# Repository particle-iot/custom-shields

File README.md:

custom-shields
==============

Collection of design files for the Spark powered custom shields

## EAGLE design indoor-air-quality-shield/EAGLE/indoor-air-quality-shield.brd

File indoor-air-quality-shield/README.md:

# Indoor Air Quality Shield

### Specifications:
 * Sensors:
 	1. Figaro TGS 2602 VOC Sensor
 	2. MICS-5525 Carbon Monoxide (CO) Sensor
 	3. DHT22 Humidity and Temperature Sensor
 	4. 2 Sockets of MQ Series Sensors
 	5. 2 Ports for Grove Sensors
 * User defined RGB LED
 * Two calibration buttons
 * Serial Port breakout headers
 * On-board DC-DC 5V power regulator

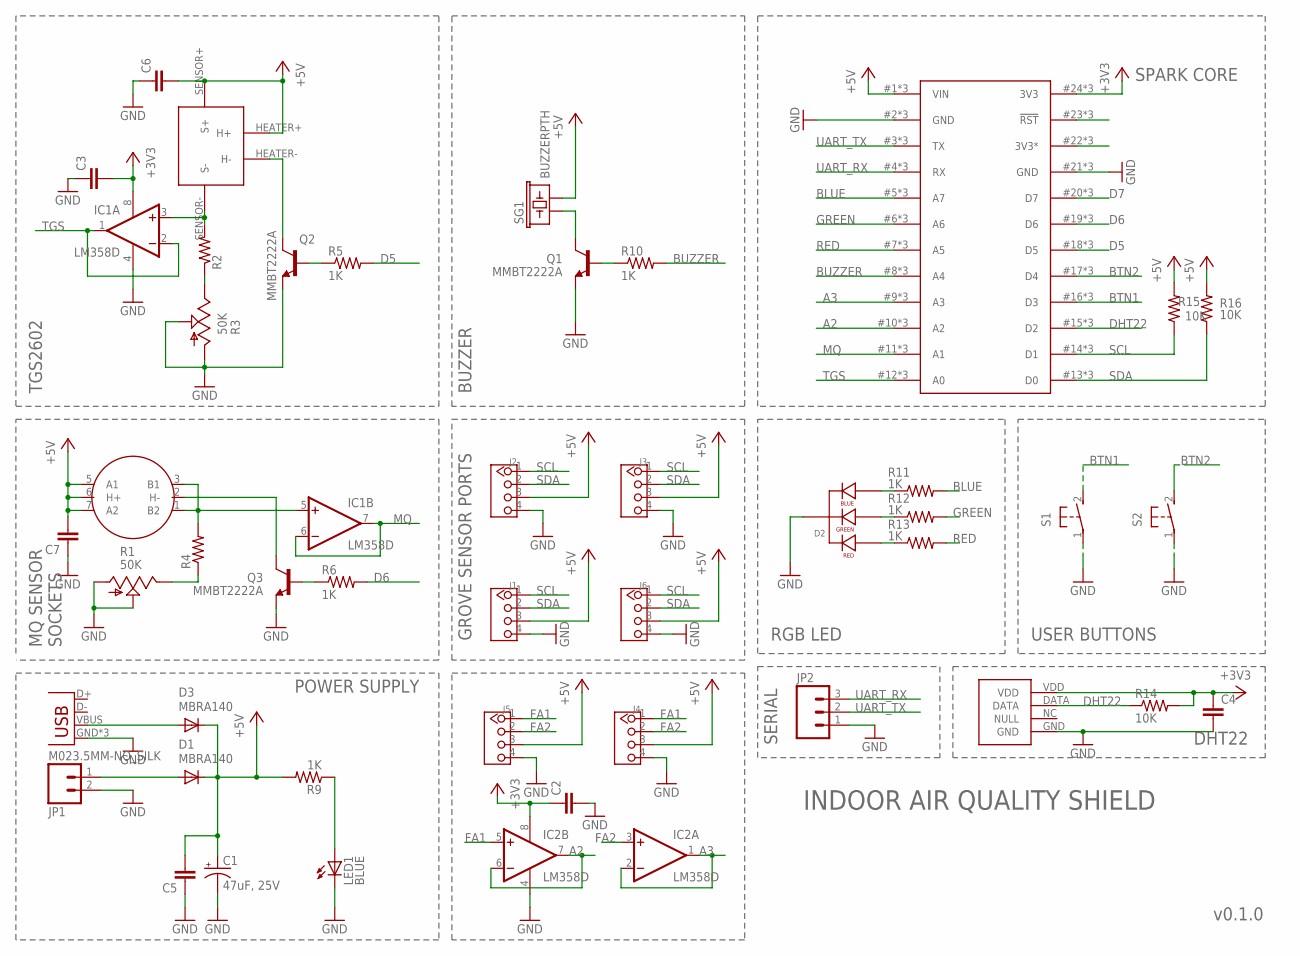
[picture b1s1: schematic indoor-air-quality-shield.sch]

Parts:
C1: 47uF, 25V; PANASONIC_D
C2, C3, C4, C5, C6, C7: C-EUC0603; C0603
D1, D3: MBRA140; SMA-DIODE
D2: LED-RGB-CC-THRUCLEAR; LED-RGB-THRU
IC1, IC2: LM358D; SO08
J1, J2, J3, J4, J5, J6: TWIG-4P-2.0'D90'; 4P-2.0-90D-W/O-BUCKLE
JP1: M023.5MM-NO_SILK; SCREWTERMINAL-3.5MM-2-NS
JP2: M03PTH; 1X03
JP3: USBUSB-MICROB-SLOT-HOLE; USB-MICROB-SLOT-HOLE
LED1: BLUE; LED-0603
Q1, Q2, Q3: MMBT2222A; SOT23-3
R1, R3: 50K; RJ9W
R2, R4: RESISTOR0603; 0603-RES
R5, R6, R9, R10, R11, R12, R13: 1K; 0603-RES
R14, R15, R16: 10K; 0603-RES
S1, S2: 31-XX; B3F-31XX
SG1: BUZZERPTH; BUZZER-12MM
U$1: TGS2602
U$2: MQ_SENSOR_SOCKET
U$5: DHT22
U$6: SPARK_CORE; SPARK_CORE_STACKABLE

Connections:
+3V3: C2.1, C3.2, C4.1, IC1.8 (V+), IC2.8 (V+), R14.2, U$5.VDD, U$6.24 (3V3), U$6.#24 (3V3), U$6.@24 (3V3)
+5V: C1.+, C5.2, C6.2, C7.2, D1.C, D3.C, J1.3, J2.3, J3.3, J4.3, J5.3, J6.3, R9.2, R15.2, R16.2, SG1.- (2), U$1.HEATER+ (H+), U$1.SENSOR+ (S+), U$2.5 (A1), U$2.6 (H+), U$2.7 (A2), U$6.1 (VIN), U$6.#1 (VIN), U$6.@1 (VIN)
A2: IC2.6 (-IN), IC2.7 (OUT), U$6.10 (A2), U$6.#10 (A2), U$6.@10 (A2)
A3: IC2.1 (OUT), IC2.2 (-IN), U$6.9 (A3), U$6.#9 (A3), U$6.@9 (A3)
BLUE: R11.2, U$6.5 (A7), U$6.#5 (A7), U$6.@5 (A7)
BTN1: S1.2 (S), U$6.16 (D3), U$6.#16 (D3), U$6.@16 (D3)
BTN2: S2.2 (S), U$6.17 (D4), U$6.#17 (D4), U$6.@17 (D4)
BUZZER: R10.2, U$6.8 (A4), U$6.#8 (A4), U$6.@8 (A4)
D5: R5.2, U$6.18 (D5), U$6.#18 (D5), U$6.@18 (D5)
D6: R6.2, U$6.19 (D6), U$6.#19 (D6), U$6.@19 (D6)
D7: U$6.20 (D7), U$6.#20 (D7), U$6.@20 (D7)
DHT22: R14.1, U$5.DATA, U$6.15 (D2), U$6.#15 (D2), U$6.@15 (D2)
FA1: IC2.5 (+IN), J4.1, J5.1
FA2: IC2.3 (+IN), J4.2, J5.2
GND: C1.-, C2.2, C3.1, C4.2, C5.1, C6.1, C7.1, D2.2 (CATHODE), IC1.4 (V-), IC2.4 (V-), J1.4, J2.4, J3.4, J4.4, J5.4, J6.4, JP1.2, JP2.1, JP3.GND, JP3.MT1 (GND), JP3.MT2 (GND), LED1.C, Q1.2 (E), Q2.2 (E), Q3.2 (E), R1.A, R1.S, R3.A, R3.S, S1.1, S2.1, U$5.GND, U$6.2 (GND), U$6.21 (GND), U$6.#2 (GND), U$6.#21 (GND), U$6.@2 (GND), U$6.@21 (GND)
GREEN: R12.2, U$6.6 (A6), U$6.#6 (A6), U$6.@6 (A6)
MQ: IC1.6 (-IN), IC1.7 (OUT), U$6.11 (A1), U$6.#11 (A1), U$6.@11 (A1)
unnamed: D2.4 (BLUE_CATHODE), R11.1
unnamed: D2.3 (GREEN_CATHODE), R12.1
unnamed: D2.1 (RED_CATHODE), R13.1
unnamed: R2.1, R3.E
unnamed: U$6.23 (!RST), U$6.#23 (!RST), U$6.@23 (!RST)
unnamed: D1.A, JP1.1
unnamed: Q3.3 (C), U$2.2 (H-)
unnamed: R1.E, R4.1
unnamed: U$6.22 (3V3*), U$6.#22 (3V3*), U$6.@22 (3V3*)
unnamed: D3.A, JP3.VBUS
unnamed: IC1.3 (+IN), R2.2, U$1.SENSOR- (S-)
unnamed: Q3.1 (B), R6.1
unnamed: Q1.1 (B), R10.1
unnamed: LED1.A, R9.1
unnamed: Q1.3 (C), SG1.+ (1)
unnamed: Q2.3 (C), U$1.HEATER- (H-)
unnamed: Q2.1 (B), R5.1
unnamed: IC1.5 (+IN), R4.2, U$2.1 (B2), U$2.3 (B1)
RED: R13.2, U$6.7 (A5), U$6.#7 (A5), U$6.@7 (A5)
SCL: J1.1, J2.1, J3.1, J6.1, R15.1, U$6.14 (D1), U$6.#14 (D1), U$6.@14 (D1)
SDA: J1.2, J2.2, J3.2, J6.2, R16.1, U$6.13 (D0), U$6.#13 (D0), U$6.@13 (D0)
TGS: IC1.1 (OUT), IC1.2 (-IN), U$6.12 (A0), U$6.#12 (A0), U$6.@12 (A0)
UART_RX: JP2.3, U$6.4 (RX), U$6.#4 (RX), U$6.@4 (RX)
UART_TX: JP2.2, U$6.3 (TX), U$6.#3 (TX), U$6.@3 (TX)

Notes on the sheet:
POWER SUPPLY
BUZZER
GROVE SENSOR PORTS
RGB LED
USER BUTTONS
DHT22
MQ SENSOR SOCKETS
TGS2602
SPARK CORE
SERIAL
INDOOR AIR QUALITY SHIELD
v0.1.0

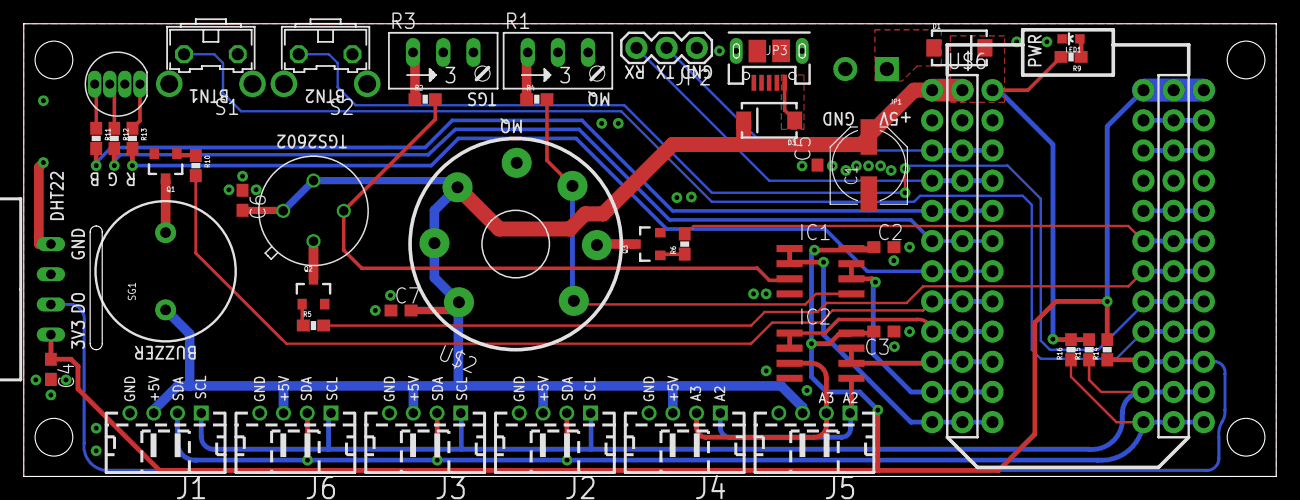
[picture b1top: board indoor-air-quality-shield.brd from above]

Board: 2 copper layers, 105.4 x 38.1 mm, 47 parts (0 on the bottom side), 41 nets.

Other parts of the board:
U$3: SPARK_LOGO2

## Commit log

2014-03-13 added indoor air quality shield files
2014-03-18 upadted pcb layout
2014-03-25 layed out indoor air quality pcb
2014-03-26 Added Bill of Materials and Gerbers
2014-03-27 Realized the BOM was for the wrong part
    This is the Shield Shield BOM—oops!
2015-03-09 updated aq shield
2015-03-10 added labels and did cleanup
2015-03-11 added bypass caps and labeled connectors
2015-03-11 created gerbers
2025-08-20 Add CC-BY-SA license

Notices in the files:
parts and their libraries:
SparkFun-Passives: Licensing: CC v3.0 Share-Alike You are welcome to use this library for commercial purposes.
